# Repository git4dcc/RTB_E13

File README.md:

# RTB_E13

This E13 module implements a 12 channel WS2811 emulator with compatible bus timing to drive multiplex (charlieplexing) LEDs. The E13 may be cascaded with regular WS28xx chips. The number of LEDs attached is automatically detected (0-12). This module allows the common LED voltage be dynamically adjusted via the bus protocol. The intended use is to drive Multiplex Signals on Model Railway layouts via the WS28xx bus.

_Note: The RTB_E13 is nearly identical to the [RTB_E15](/../../../../git4dcc/RTB_E15) but allows for variable LED voltage._

<details>
<summary>See also</summary>

- [RTB_E10](/../../../../git4dcc/RTB_E10)
- [RTB_E15](/../../../../git4dcc/RTB_E15)

</details>

<details>
<summary>User Guides</summary>

- [User Guide - DE](https://rtb4dcc.de/ws2811_guide_de/)
- User Guide - EN

</details>

The decoder has the following features,
- **Protocol**
  - WS2811 compatible timing
- **LED ports**
  - 12 channel output
  - Charlieplexing (Multiplexing) output
  - 128 step PWM (300Hz)
  - Software adjustable LED voltage 0..5V (see also [RTB_E15](/../../../../git4dcc/RTB_E15))
  - gamma correction (optional)
- firmware update via V24 debug interface

# Hardware
My current PCB layout uses SMD footprints with 0.5mm pitch and 0603 parts. Reflow soldering is my recommendation, but with some experience handsoldering is also possible.

## PCB
- 2-layer PCB, FR4, 1.6mm
- CPU: AVR64DB32
- BUS: WS28xx
- LED: Charlieplexing

## Kicad
[Schematic](doc/E13_schematic.pdf) | [Layout](doc/E13_layout.pdf) | [Gerber](gerber)

<details>
<summary>Dependency</summary>
<br>
  
:yellow_circle: Requires my Kicad project library [RTB_SamacSys](/../../../../git4dcc/RTB_SamacSys) in the same directory tree.

</details>

## Firmware
Filename structure: { **pcb** }{ **code** }{ **version** }.hex

Example: **E13F0001**.hex

|   | Description |
| --- | --- |
| **pcb** | Name of matching hardware (**E13**) |
| **code** | Type of code contained (**R**=rom, **B**=bootloader, **F**=flash, **U**=bld update, **P**=UPDI factory code) |
| **version** | Release version (**####**) |

## UPDI
The fuse settings as well as the P-code (E13Pxxxx.hex) has to be installed by using UPDI.<br>

<details>
<summary>Details</summary>

| Fuse Setting | P-code Install |
| --- | --- |
|||

</details>

## Debug Interface
Subsequent code updates can be done via the built-in serial debug interface.<br>

<details>
<summary>Details</summary>

- connect the serial cable **(1Mb, 8N1, RTS/CTS)**
- press 'break' within the VT100 terminal to bump the module to console prompt
- upload the firmware file (E13Fxxxx.hex)
- for more details, refer to the 'User Guide'

</details>

# Software
The LED common voltage must be sent as the first byte (virtual LED) over the bus followed by the intensity values for the individual LEDs, with N being the number of configured LEDs.
```
Byte order:     {voltage} {led_0} ... {led_N}
Led Voltage:    5V * {voltage} / 255
```

# Images

This project is intended for hobby use only and is distributed in accordance with the Apache License 2.0 agreement.

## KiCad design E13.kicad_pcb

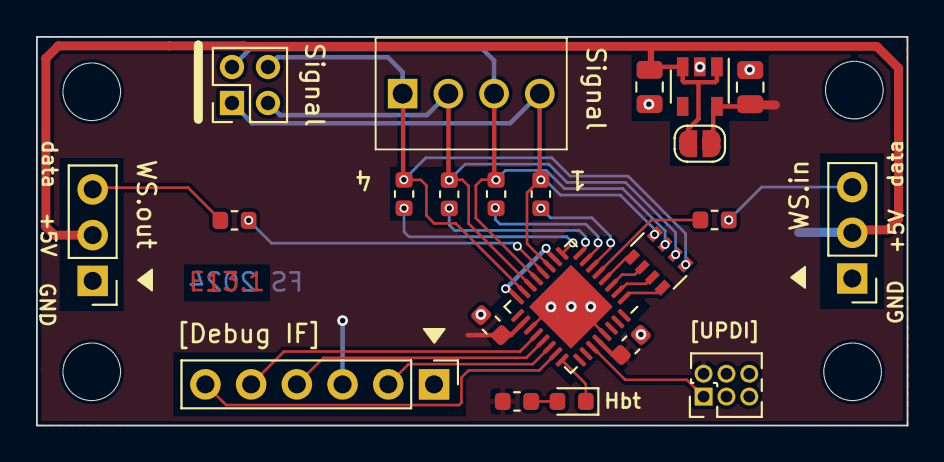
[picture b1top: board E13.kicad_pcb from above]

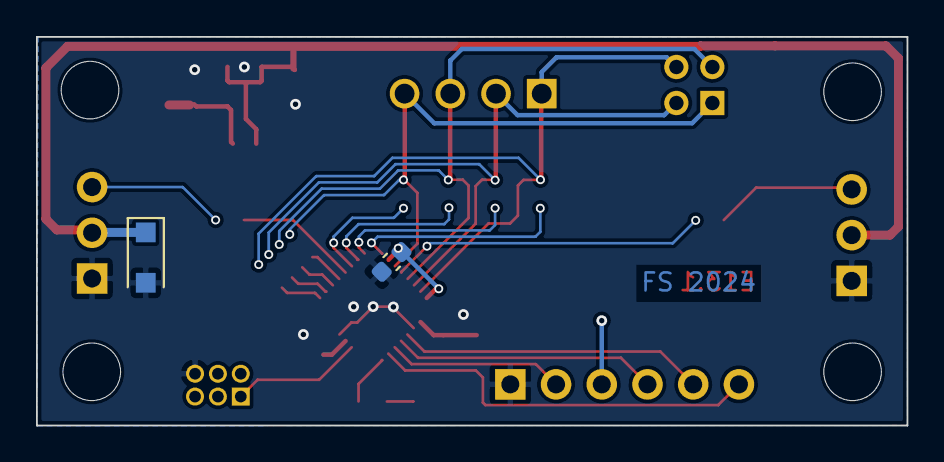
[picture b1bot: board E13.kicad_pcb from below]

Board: 2 copper layers, 48.4 x 21.6 mm, 28 parts (2 on the bottom side), 27 nets.

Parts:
C1, C4: 4.7u/10V; C_0805_2012Metric
C2, C3, C5: 100n; C_0603_1608Metric
D1: SSL34F; D_SOD-123F
D2: HBT(green); LED_0603_1608Metric
H1, H2, H3, H4: MountingHole; MountingHole_3.2mm_M3_DIN965
IC1: AVR64DB32-I_RXB; QFN-32-1EP_5x5mm_P0.5mm_EP3.3x3.3mm
J1: Multiplex out; PinHeader_2x02_P2.00mm_Vertical
J2: WS-bus output; PinHeader_1x03_P2.54mm_Vertical
J3: WS-bus input; PinHeader_1x03_P2.54mm_Vertical
J4: UPDI; PinHeader_2x03_P1.27mm_Vertical
J5: Debug IF; PinHeader_1x06_P2.54mm_Vertical
J7: Multiplex out; 1725672
JP1: skip LDO; SolderJumper-2_P1.3mm_Open_RoundedPad1.0x1.5mm
R14, R15, R16, R17: 120; R_0603_1608Metric
R18, R19: 160; R_0603_1608Metric
R20: 3.3k; R_0603_1608Metric
RN1: 4x 22k; R_Array_Convex_4x0603
U2: MIC5205-5.0YM5; SOT-23-5

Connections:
+5V: C1.1, D1.1, J2.2, J3.2, JP1.1, U2.1, U2.3
DAC: C5.1, IC1.10, IC1.16
DI: J3.3, R18.2
DO: J2.3, R19.2
GND: C1.2, C2.2, C3.2, C4.2, C5.2, D1.2, IC1.19, IC1.29, IC1.33, J2.1, J3.1, J4.6, J5.1, U2.2
unnamed: D2.1, IC1.24
unnamed: D2.2, R20.1
unnamed: IC1.1, RN1.4
unnamed: IC1.2, RN1.3
unnamed: IC1.3, RN1.2
unnamed: IC1.4, RN1.1
unnamed: IC1.5, R18.1
unnamed: IC1.6, R16.1
unnamed: IC1.7, R17.1
unnamed: IC1.8, R15.1
unnamed: IC1.9, R14.1
unnamed: IC1.12, R19.1
OUT1: IC1.11, J1.1, J7.4, R16.2, RN1.8
OUT2: IC1.13, J1.2, J7.3, R17.2, RN1.7
OUT3: IC1.14, J1.3, J7.2, R15.2, RN1.6
OUT4: IC1.15, J1.4, J7.1, R14.2, RN1.5
UPDI: IC1.27, J4.1
V24.cts: IC1.23, J5.6
V24.rts: IC1.22, J5.2
V24.rx: IC1.21, J5.4
V24.tx: IC1.20, J5.5
VDD: C2.1, C3.1, C4.1, IC1.18, IC1.28, J4.2, J5.3, JP1.2, R20.2, U2.5

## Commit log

2024-02-23 initial
2024-10-04 Added local images
2024-11-14 mod: documentation
2026-02-20 git mirror test

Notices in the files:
E13.kicad_pcb:
Licensed under the Apache License, Version 2
